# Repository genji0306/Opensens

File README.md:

# Opensens
Opensource Potentiostat
Sau khi chia sẻ điện cực in SPE, Lab em đã nhận được sự nhiều sự quan tâm và liên hệ. Nhóm em nhận thấy là hiện tại việc nghiên cứu về Electrochemistry và Biosensor của các nhóm nghiên cứ ở trong VN còn nhiều khó khăn đặt biệt là về vấn đề thiết bị. Chính vì vậy, lab em quyết định chia sẻ phần nghiên cứu về thiết bị đo điện hoá Potentiostat/Galvanostat cho mọi người, hy vọng có thể giảm bớt khó khăn khi nghiên cứu trong nước Potentiostat/Galvanostat do nhóm DYNLAB- PGS. Thuỷ, thuộc Bộ Môn Điện Hoá, Đại Học Bách Khoa Hà Nội và nhóm PGS. Nguyên, ĐH KHTN HCM - phát triển – tên mã project là OEPS – tên chính thức là Opensens, được phát triển từ cuối năm 2017 với mục tiêu là tạo ra thiết bị đo điện hoá nhỏ gọn tin cậy độ phân giải cao, giá thành hợp lý để triển khai giám sát trên diện rộng. Version đầu tiên dựa trên phiên bản của TS. Dobbelaere và bản sau này của Irving (NCS của Dobbelaere). Phiên bản OEPS V1 dựa trên hardware với một số thay đổi về linh kiện, firmware và phần mềm. Sau 5 năm nghiên cứu, hiện nhóm đã phát triển nhiều Version khác nhau phục vụ cho nghiên cứu về Nguồn điện (Pin), Cảm Biến và giám sát môi trường. 
Trong link chia sẻ là bản OEPS V1/V2, MFO V1 và cả Software gốc/ Software của lab: 
- OEPS V1: Gồm một số tính năng: LSV, CV, CP, CA, Phóng nạp Pin - dải điện áp +-8V 30mA - hiệu chỉnh lỗi và tương thích software bản mới. (DAC 22 bits - độ phân giải 4pA) 
- OEPS V2: Dải điện áp +-12V 250mA - modify chống nhiễu, thay đổi linh kiện giá hợp lý hơn và chỉnh sửa lại Software.
- MFO V1: Phiên bản rút gọn đo 1 phép đo set up sẵn dùng cho y sinh/ môi trường. Có khả năng đo được hầu hết các phép đo LSV,CV,CP,CA, DPV, NPV, EIS(<34khz) (độ phân giải thấp – 12 bits) 
Các phiên bản trên đã được chạy thử nghiệm ít nhất 2 năm và nhiều nhất là từ khi dự án được tiến hành, đã so sánh với thiết bị thương mại như Autolab, Biologic và Palmsens. Các phiên bản khác của lab được tích hơn thêm Pulse technique và EIS sẽ sớm được opensource trong thời gian tiếp theo. Nếu muốn trải nghiệm thiết bị, xin mời mọi người qua DHBK HN ở Hà Nội gặp và Trường DH KHTN HCM ở HCM gặp PGS. Nguyên .

Chi phí linh kiện của thiết bị dao động từ $120-150, tuy nhiên thực tế tuỳ số lượng, đơn vị gia công và thuế nhập khẩu, chi phí sx rơi vào tầm 5-8tr/ thiết bị. Mọi người chỉ cần gửi link và liên hệ bên điện điện tử là được. Cũng chia sẻ luôn, tầm giữa tháng 4 tại bên lab sẽ đặt thêm linh kiện và gia công thiết bị (phiên bản mới) nhưng có chung nhiều linh kiện phiên bản cũ. Vì vậy nếu cần thì bên em có thể đặt giúp mọi người. Chi tiết xin liên hệ sdt: 033. 616.4867 

Ps: do phải tách repo Git để opensource nên dữ liệu sẽ được upload dần từ giờ tới cuối tuần

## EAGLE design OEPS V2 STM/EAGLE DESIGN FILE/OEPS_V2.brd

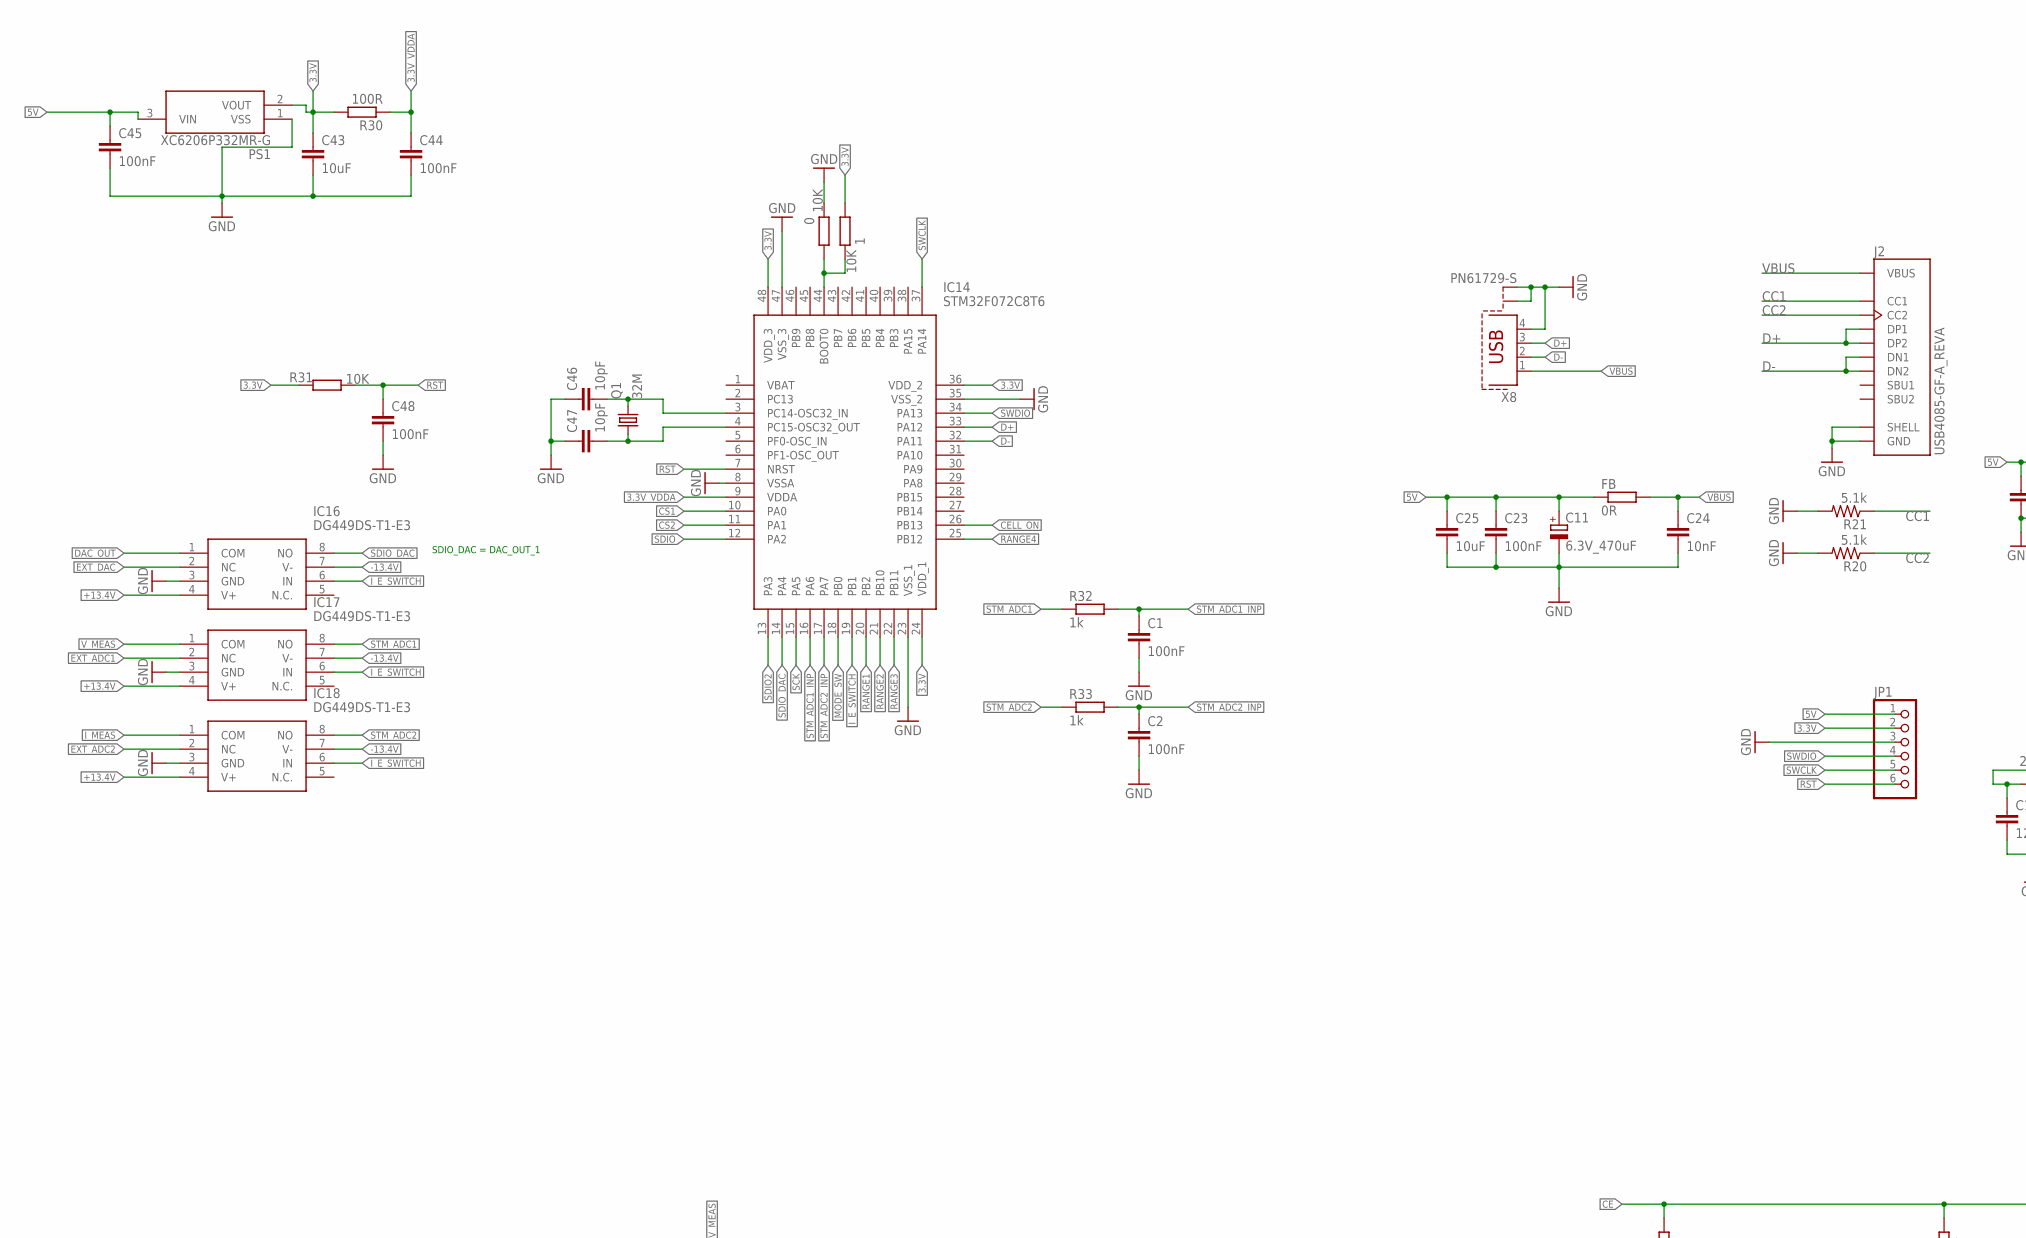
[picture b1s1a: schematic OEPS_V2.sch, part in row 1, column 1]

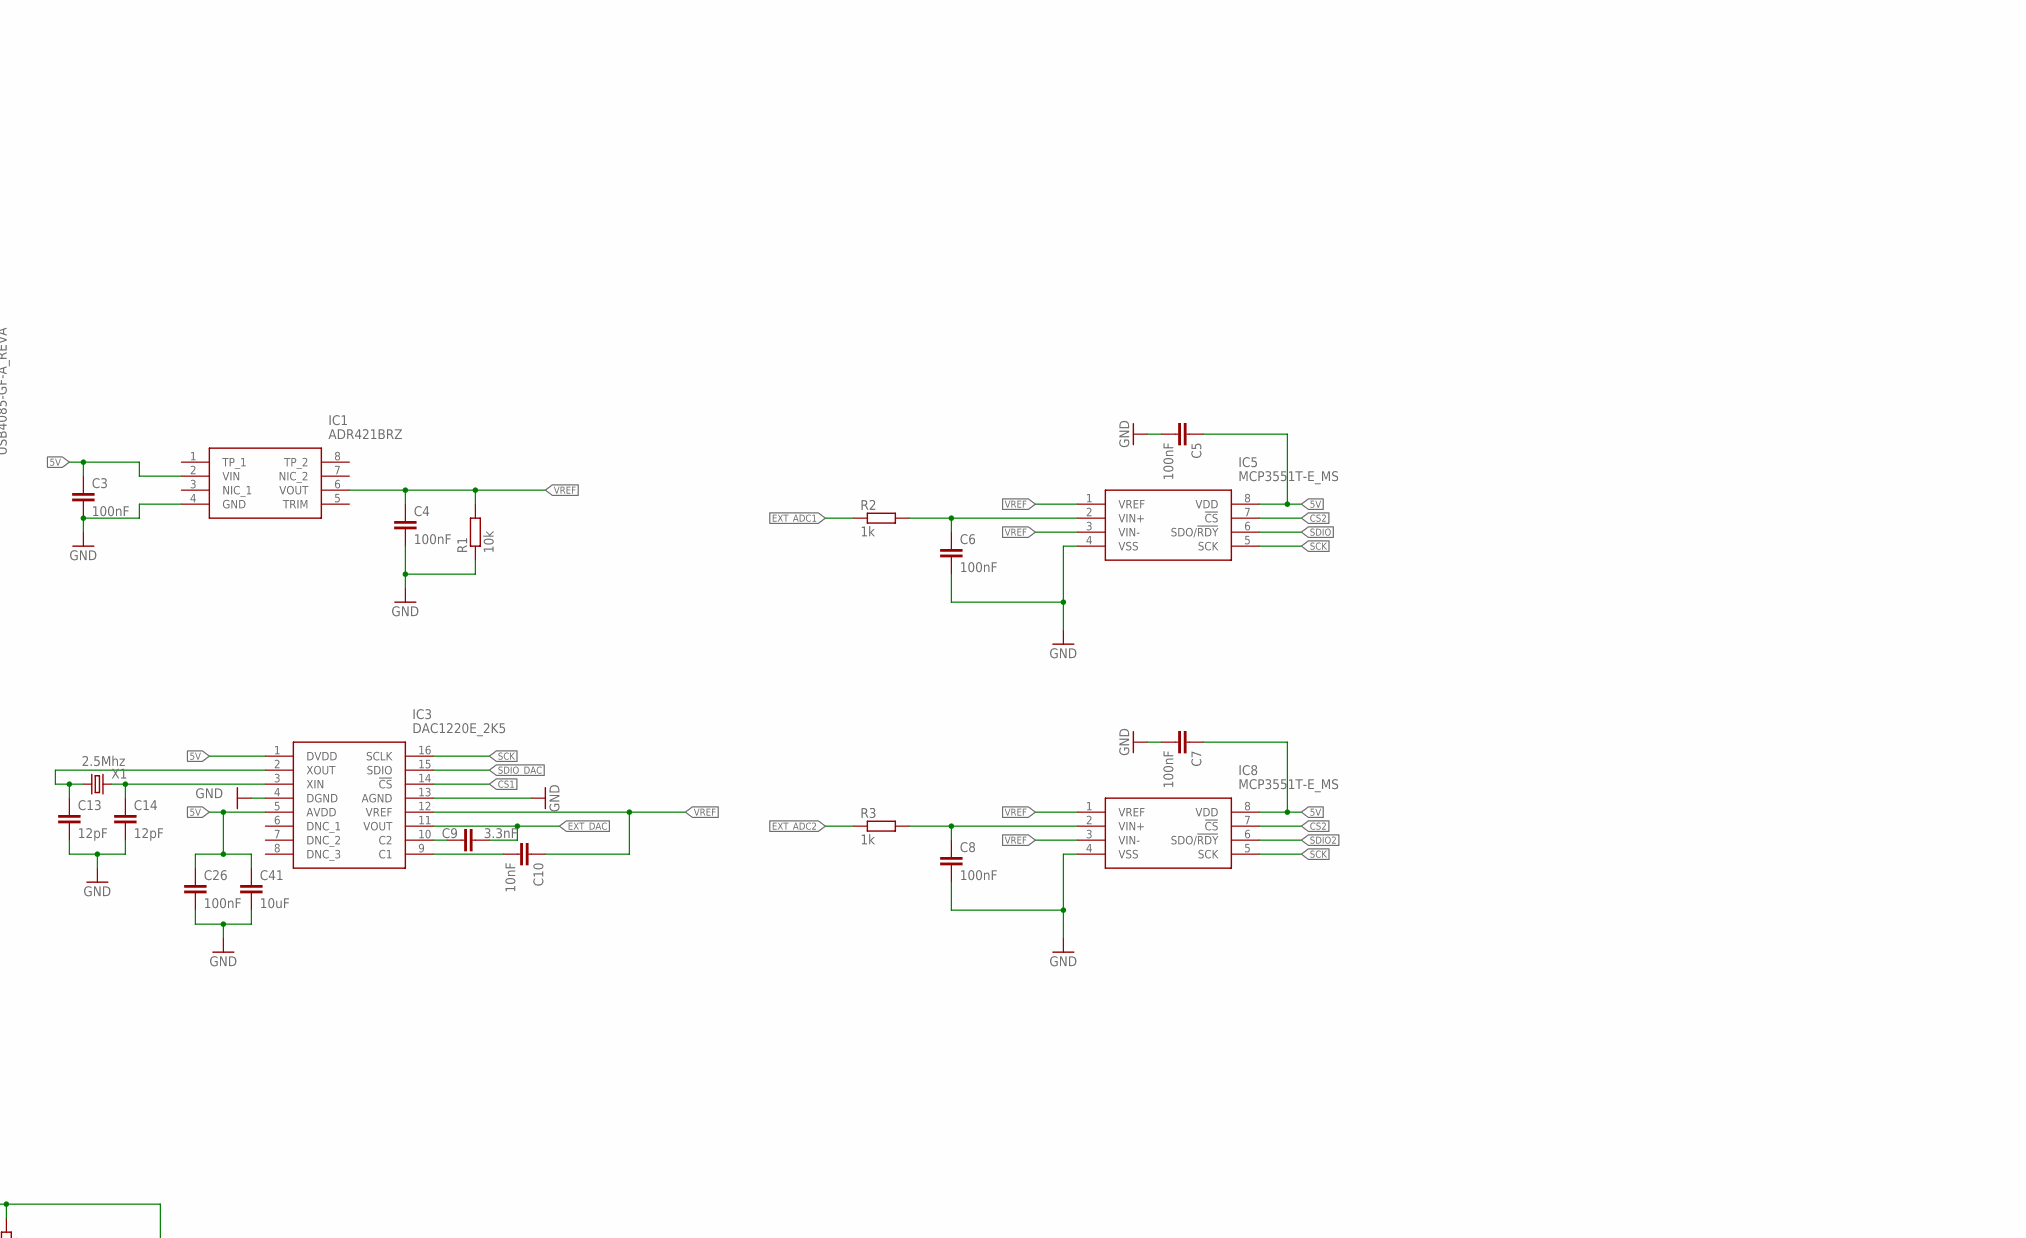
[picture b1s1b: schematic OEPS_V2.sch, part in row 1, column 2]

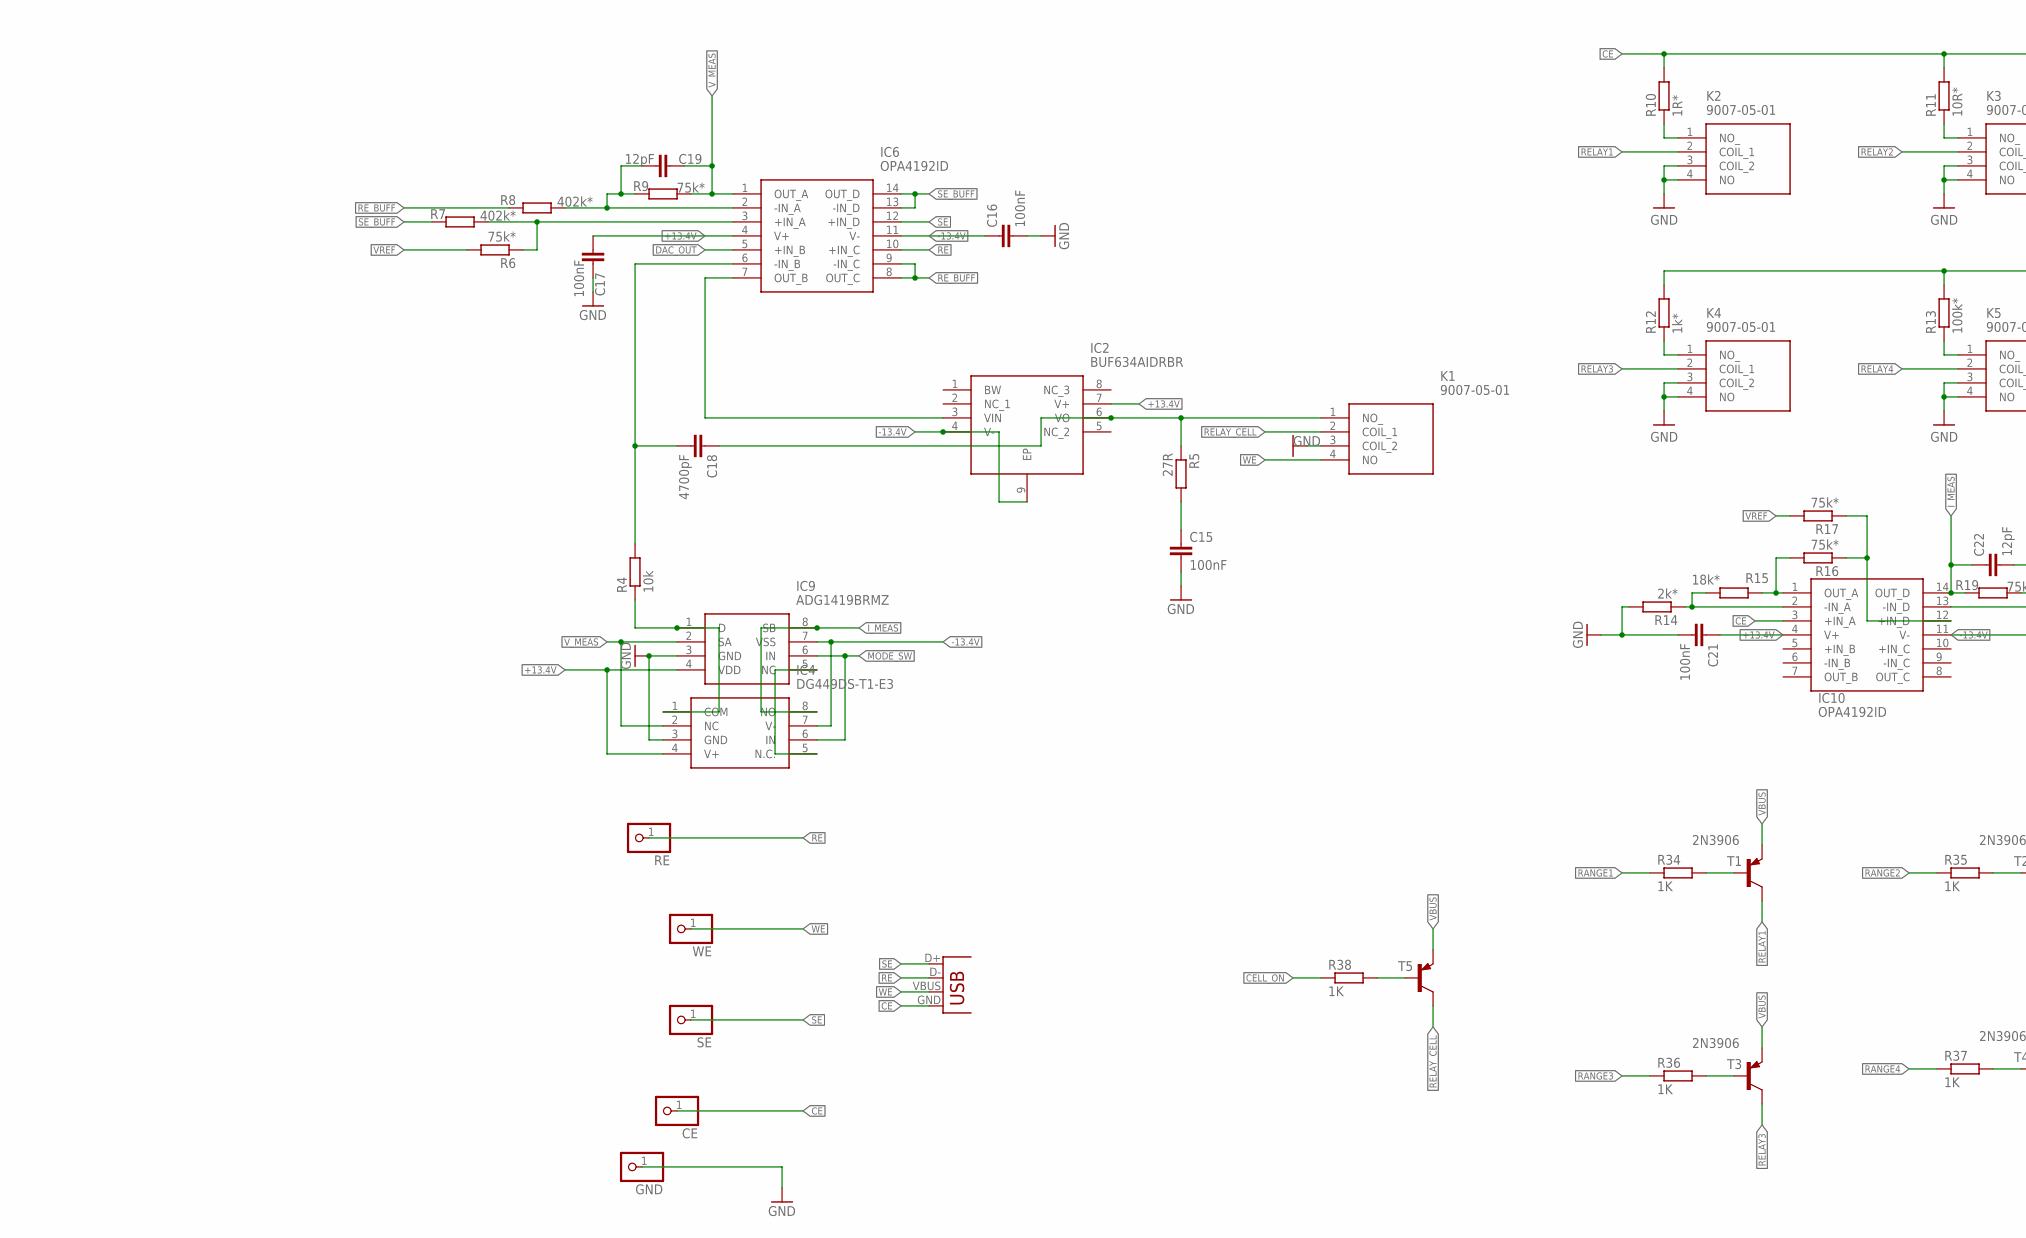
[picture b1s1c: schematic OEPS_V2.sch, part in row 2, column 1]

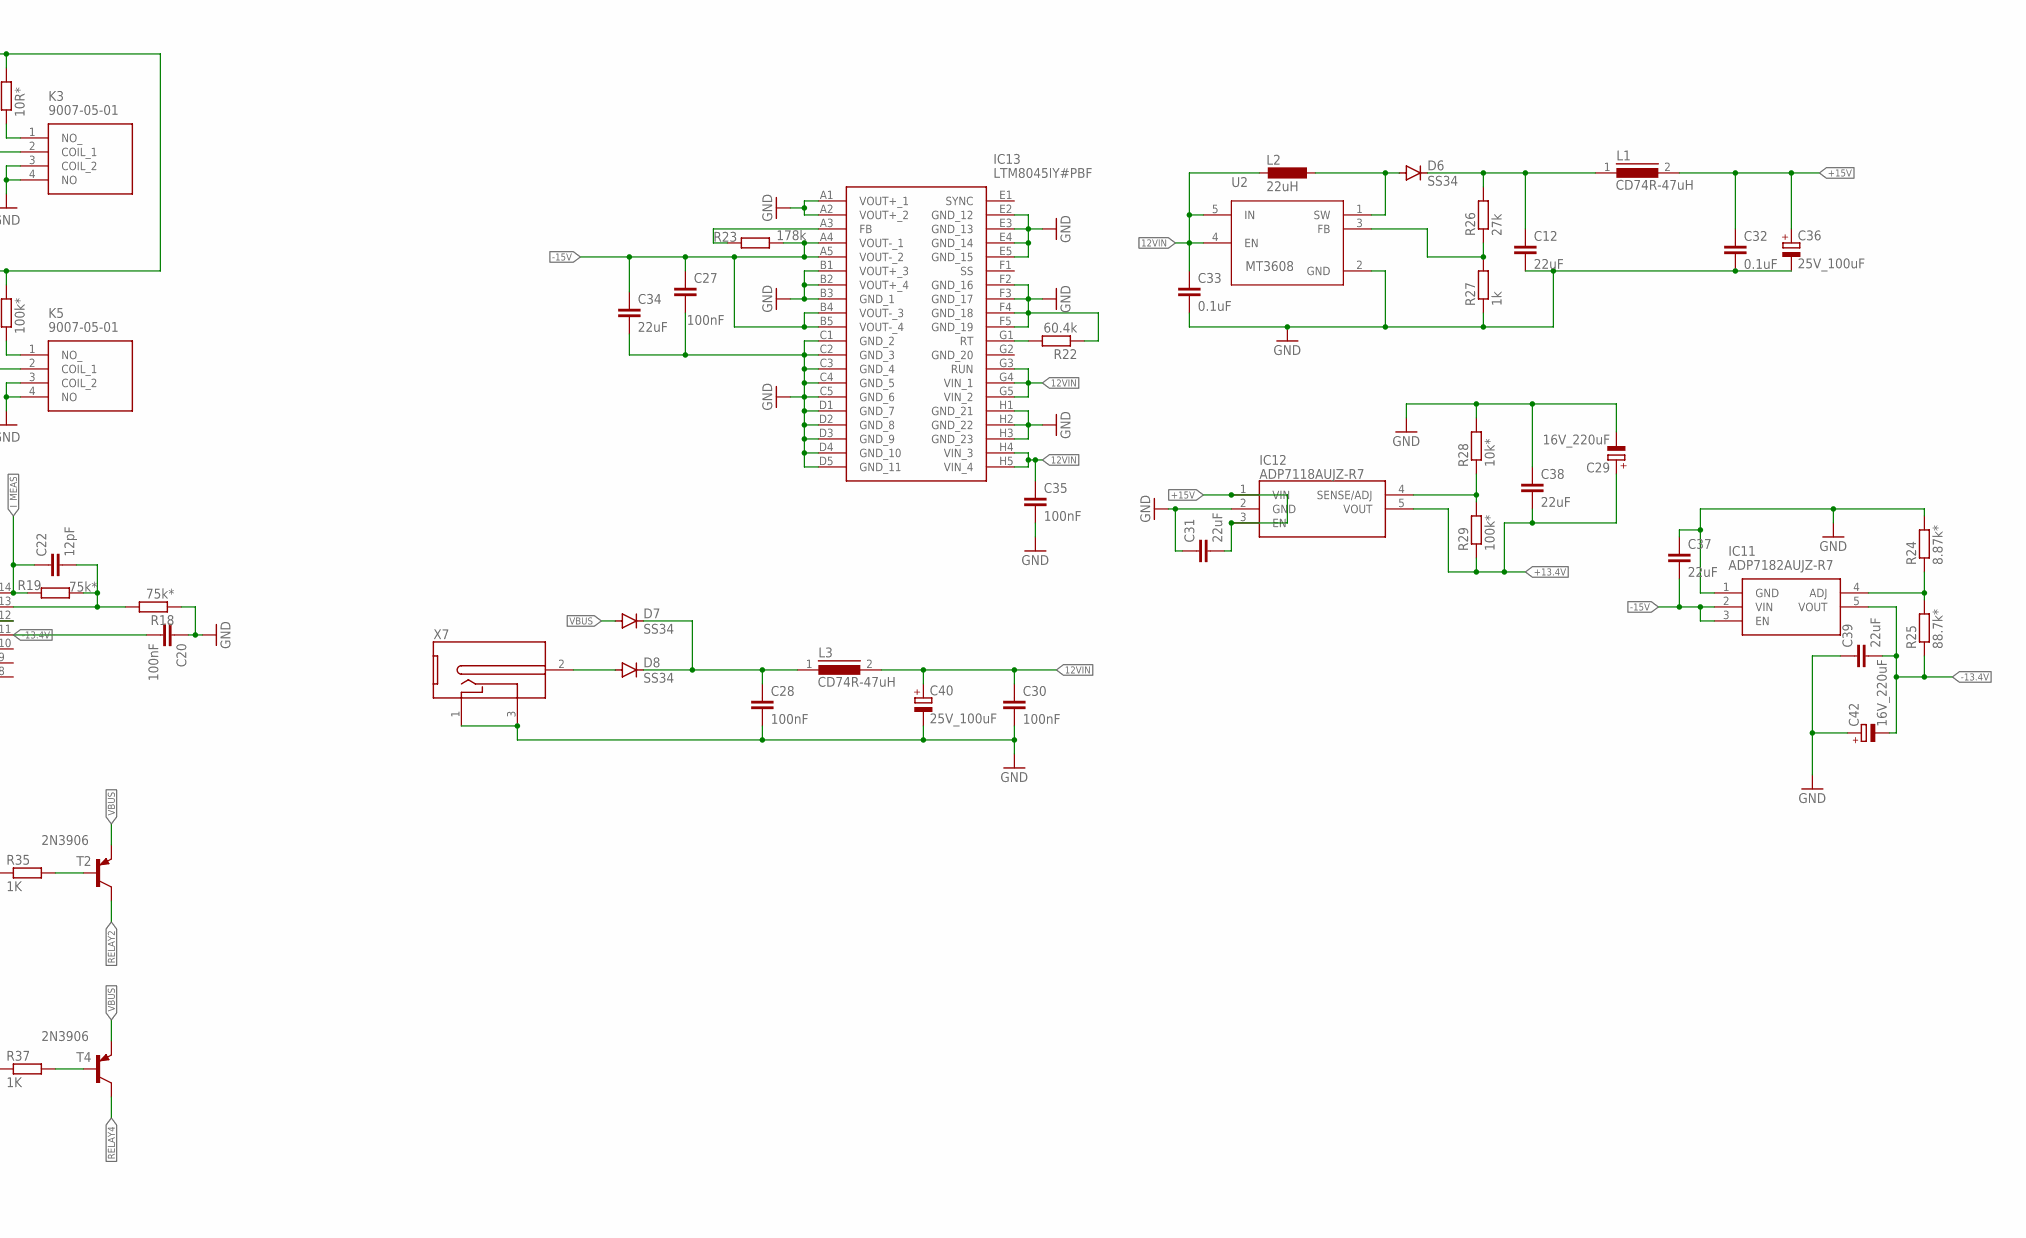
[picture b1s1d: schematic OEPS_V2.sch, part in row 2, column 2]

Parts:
0, 1: 10K; R0603
C1, C2, C3, C4, C5, C6, C7, C8, C15, C16, C17, C20, C21, C23, C26, C44, C45, C48: 100nF; C0603
C9: 3.3nF; C0603
C10, C24: 10nF; C0603
C11: 6.3V_470uF; 153CLV-0605
C12, C31, C34, C37, C38, C39: 22uF; C1206
C13, C14, C19, C22: 12pF; C0603
C18: 4700pF; C0603
C25, C41, C43: 10uF; C0603
C27, C28, C30, C35: 100nF; C0805
C29, C42: 16V_220uF; 153CLV-0605
C32, C33: 0.1uF; C0805
C36, C40: 25V_100uF; 153CLV-0605
C46, C47: 10pF; C0603
CE: PINHD-1X1; 1X01
D6, D7, D8: SS34; DO-214AC
FB: 0R; R0805
GND: PINHD-1X1; 1X01
IC1: ADR421BRZ; SOIC127P600X175-8N
IC2: BUF634AIDRBR; SON65P300X300X100-9N
IC3: DAC1220E_2K5; SOP64P600X175-16N
IC4, IC16, IC17, IC18: DG449DS-T1-E3; SOP65P280X145-8N
IC5, IC8: MCP3551T-E_MS; SOP65P490X110-8N@1
IC6, IC10: OPA4192ID; SOIC127P600X175-14N
IC9: ADG1419BRMZ; SOP65P490X110-8N
IC11: ADP7182AUJZ-R7; SOT95P280X100-5N
IC12: ADP7118AUJZ-R7; SOT95P280X100-5N
IC13: LTM8045IY#PBF; BGA40C127P5X8_625X1125X512
IC14: STM32F072C8T6; QFP50P900X900X160-48N
J2: USB4085-GF-A_REVA; GCT_USB4085-GF-A_REVA
JP1: PINHD-1X6; 1X06
K1, K2, K3, K4, K5: 9007-05-01; 90070501
L1, L3: CD74R-47uH; DR74
L2: 22uH; PIS2816
PS1: XC6206P332MR-G; SOT95P280X130-3N
Q1: 32M; 3.2X2.5_KX-7
R1, R4: 10k; R0603
R2, R3, R27, R32, R33: 1k; R0603
R5: 27R; R0603
R6, R9, R16, R17, R18, R19: 75k*; R0603
R7, R8: 402k*; R0603
R10: 1R*; R0805
R11: 10R*; R0805
R12: 1k*; R0805
R13: 100k*; R0805
R14: 2k*; R0603
R15: 18k*; R0603
R20, R21: 5.1k; R0603
R22: 60.4k; R0603
R23: 178k; R0603
R24: 8.87k*; R0603
R25: 88.7k*; R0603
R26: 27k; R0603
R28: 10k*; R0603
R29: 100k*; R0603
R30: 100R; R0603
R31: 10K; R0603
R34, R35, R36, R37, R38: 1K; R0603
RE: PINHD-1X1; 1X01
SE: PINHD-1X1; 1X01
T1, T2, T3, T4: 2N3906; SOT23-BEC
T5: MMBT3906LT1-PNP-SOT23-BEC; SOT23-BEC
U2: MT3608; SOT95P280X145-6N
WE: PINHD-1X1; 1X01
X1: 2.5Mhz; HC49
X6: USB-A-H
X7: DC-2.1MM-5MM; DC-21MM
X8: PN61729-S

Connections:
3.3V: 1.2, C43.1, IC14.24 (VDD_1), IC14.36 (VDD_2), IC14.48 (VDD_3), JP1.2, PS1.2 (VOUT), R30.2, R31.2
3.3V_VDDA: C44.1, IC14.9 (VDDA), R30.1
5V: C3.1, C5.1, C7.1, C11.+, C23.1, C25.1, C26.1, C41.1, C45.1, FB.1, IC1.2 (VIN), IC3.1 (DVDD), IC3.5 (AVDD), IC5.8 (VDD), IC8.8 (VDD), JP1.1, PS1.3 (VIN)
12VIN: C30.1, C33.1, C35.1, C40.+, IC13.G3 (RUN), IC13.G4 (VIN_1), IC13.G5 (VIN_2), IC13.H4 (VIN_3), IC13.H5 (VIN_4), L2.2, L3.2, U2.4 (EN), U2.5 (IN)
+13.4V: C17.2, C21.1, C29.+, C38.2, IC2.7 (V+), IC4.4 (V+), IC6.4 (V+), IC9.4 (VDD), IC10.4 (V+), IC12.5 (VOUT), IC16.4 (V+), IC17.4 (V+), IC18.4 (V+), R29.1
+15V: C31.2, C32.1, C36.+, IC12.1 (VIN), IC12.3 (EN), L1.2
-13.4V: C16.1, C20.1, C39.2, C42.-, IC2.4 (V-), IC2.9 (EP), IC4.7 (V-), IC6.11 (V-), IC9.7 (VSS), IC10.11 (V-), IC11.5 (VOUT), IC16.7 (V-), IC17.7 (V-), IC18.7 (V-), R25.1
-15V: C27.1, C34.1, C37.2, IC11.2 (VIN), IC11.3 (EN), IC13.A4 (VOUT-_1), IC13.A5 (VOUT-_2), IC13.B4 (VOUT-_3), IC13.B5 (VOUT-_4), R23.2
CC1: J2.A5 (CC1), R21.1
CC2: J2.B5 (CC2), R20.1
CE: CE.1, IC10.3 (+IN_A), R10.2, R11.2, R12.2, R13.2, X6.GND
CELL_ON: IC14.26 (PB13), R38.1
CS1: IC3.14 (!CS), IC14.10 (PA0)
CS2: IC5.7 (!CS), IC8.7 (!CS), IC14.11 (PA1)
D+: IC14.33 (PA12), J2.A6 (DP1), J2.B6 (DP2), X8.3
D-: IC14.32 (PA11), J2.A7 (DN1), J2.B7 (DN2), X8.2
DAC_OUT: IC6.5 (+IN_B), IC16.1 (COM)
EXT_ADC1: IC17.2 (NC), R2.1
EXT_ADC2: IC18.2 (NC), R3.1
EXT_DAC: C9.1, IC3.11 (VOUT), IC16.2 (NC)
GND: 0.1, C1.2, C2.2, C3.2, C4.2, C5.2, C6.2, C7.2, C8.2, C11.-, C12.2, C13.2, C14.2, C15.2, C16.2, C17.1, C20.2, C21.2, C23.2, C24.2, C25.2, C26.2, C27.2, C28.2, C29.-, C30.2, C31.1, C32.2, C33.2, C34.2, C35.2, C36.-, C37.1, C38.1, C39.1, C40.-, C41.2, C42.+, C43.2, C44.2, C45.2, C46.1, C47.1, C48.2, GND.1, IC1.4 (GND), IC3.4 (DGND), IC3.13 (AGND), IC4.3 (GND), IC5.4 (VSS), IC8.4 (VSS), IC9.3 (GND), IC11.1 (GND), IC12.2 (GND), IC13.A1 (VOUT+_1), IC13.A2 (VOUT+_2), IC13.B1 (VOUT+_3), IC13.B2 (VOUT+_4), IC13.B3 (GND_1), IC13.C1 (GND_2), IC13.C2 (GND_3), IC13.C3 (GND_4), IC13.C4 (GND_5), IC13.C5 (GND_6), IC13.D1 (GND_7), IC13.D2 (GND_8), IC13.D3 (GND_9), IC13.D4 (GND_10), IC13.D5 (GND_11), IC13.E2 (GND_12), IC13.E3 (GND_13), IC13.E4 (GND_14), IC13.E5 (GND_15), IC13.F2 (GND_16), IC13.F3 (GND_17), IC13.F4 (GND_18), IC13.F5 (GND_19), IC13.H1 (GND_21), IC13.H2 (GND_22), IC13.H3 (GND_23), IC14.8 (VSSA), IC14.23 (VSS_1), IC14.35 (VSS_2), IC14.47 (VSS_3), IC16.3 (GND), IC17.3 (GND), IC18.3 (GND), J2.A1 (GND), J2.A12 (GND), J2.B1 (GND), J2.B12 (GND), J2.P1 (SHELL), J2.P2 (SHELL), J2.P3 (SHELL), J2.P4 (SHELL), JP1.3, K1.3 (COIL_2), K2.3 (COIL_2), K2.4 (NO), K3.3 (COIL_2), K3.4 (NO), K4.3 (COIL_2), K4.4 (NO), K5.3 (COIL_2), K5.4 (NO), PS1.1 (VSS), R1.1, R14.2, R18.1, R20.2, R21.2, R22.1, R24.2, R27.1, R28.2, U2.2 (GND), X7.1, X7.3 (2), X8.4, X8.S1, X8.S2
I_E_SWITCH: IC14.19 (PB1), IC16.6 (IN), IC17.6 (IN), IC18.6 (IN)
I_MEAS: C22.1, IC4.8 (NO), IC9.8 (SB), IC10.14 (OUT_D), IC18.1 (COM), R19.2
MODE_SW: IC4.6 (IN), IC9.6 (IN), IC14.18 (PB0)
unnamed: C6.1, IC5.2 (VIN+), R2.2
unnamed: C8.1, IC8.2 (VIN+), R3.2
unnamed: R34.2, T1.B
unnamed: C46.2, IC14.3 (PC14-OSC32_IN), Q1.3 (2)
unnamed: C14.1, IC3.3 (XIN), X1.2
unnamed: C13.1, IC3.2 (XOUT), X1.1
unnamed: C9.2, IC3.10 (C2)
unnamed: C10.2, IC3.9 (C1)
unnamed: IC4.1 (COM), IC9.1 (D), R4.1
unnamed: C18.2, IC6.6 (-IN_B), R4.2
unnamed: IC2.3 (VIN), IC6.7 (OUT_B)
unnamed: C18.1, IC2.6 (VO), K1.1 (NO_), R5.1
unnamed: C15.1, R5.2
unnamed: IC4.5 (N.C.), IC9.5 (NC)
unnamed: IC6.3 (+IN_A), R6.1, R7.1
unnamed: C19.2, IC6.2 (-IN_A), R8.1, R9.2
unnamed: K2.1 (NO_), R10.1
unnamed: IC10.1 (OUT_A), R15.1, R16.2
unnamed: K3.1 (NO_), R11.1
unnamed: IC10.2 (-IN_A), R14.1, R15.2
unnamed: K4.1 (NO_), R12.1
unnamed: C12.1, D6.C, L1.1, R26.2
unnamed: K5.1 (NO_), R13.1
unnamed: IC10.12 (+IN_D), R16.1, R17.1
unnamed: C28.1, D7.C, D8.C, L3.1
unnamed: C22.2, IC10.13 (-IN_D), R18.2, R19.1
unnamed: IC11.4 (ADJ), R24.1, R25.2
unnamed: D8.A, X7.2 (3)
unnamed: IC12.4 (SENSE/ADJ), R28.1, R29.2
unnamed: C47.2, IC14.4 (PC15-OSC32_OUT), Q1.1
unnamed: 0.2, 1.1, IC14.44 (BOOT0)
unnamed: R35.2, T2.B
unnamed: IC13.G1 (RT), R22.2
unnamed: IC13.A3 (FB), R23.1
unnamed: R36.2, T3.B
unnamed: R37.2, T4.B
unnamed: R38.2, T5.B
unnamed: D6.A, L2.1, U2.1 (SW)
unnamed: R26.1, R27.2, U2.3 (FB)
RANGE1: IC14.20 (PB2), R34.1
RANGE2: IC14.21 (PB10), R35.1
RANGE3: IC14.22 (PB11), R36.1
RANGE4: IC14.25 (PB12), R37.1
RE: IC6.10 (+IN_C), RE.1, X6.D-
RELAY1: K2.2 (COIL_1), T1.C
RELAY2: K3.2 (COIL_1), T2.C
RELAY3: K4.2 (COIL_1), T3.C
RELAY4: K5.2 (COIL_1), T4.C
RELAY_CELL: K1.2 (COIL_1), T5.C
RE_BUFF: IC6.8 (OUT_C), IC6.9 (-IN_C), R8.2
RST: C48.1, IC14.7 (NRST), JP1.6, R31.1
SCK: IC3.16 (SCLK), IC5.5 (SCK), IC8.5 (SCK), IC14.15 (PA5)
SDIO: IC5.6 (SDO/!RDY), IC14.12 (PA2)
SDIO2: IC8.6 (SDO/!RDY), IC14.13 (PA3)
SDIO_DAC: IC3.15 (SDIO), IC14.14 (PA4), IC16.8 (NO)
SE: IC6.12 (+IN_D), SE.1, X6.D+
SE_BUFF: IC6.13 (-IN_D), IC6.14 (OUT_D), R7.2
STM_ADC1: IC17.8 (NO), R32.1
STM_ADC1_INP: C1.1, IC14.16 (PA6), R32.2
STM_ADC2: IC18.8 (NO), R33.1
STM_ADC2_INP: C2.1, IC14.17 (PA7), R33.2
SWCLK: IC14.37 (PA14), JP1.5
SWDIO: IC14.34 (PA13), JP1.4
VBAT: IC14.1 (VBAT)
VBUS: C24.1, D7.A, FB.2, J2.A4 (VBUS), J2.A9 (VBUS), J2.B4 (VBUS), J2.B9 (VBUS), T1.E, T2.E, T3.E, T4.E, T5.E, X8.1
VREF: C4.1, C10.1, IC1.6 (VOUT), IC3.12 (VREF), IC5.1 (VREF), IC5.3 (VIN-), IC8.1 (VREF), IC8.3 (VIN-), R1.2, R6.2, R17.2
V_MEAS: C19.1, IC4.2 (NC), IC6.1 (OUT_A), IC9.2 (SA), IC17.1 (COM), R9.1
WE: K1.4 (NO), WE.1, X6.VBUS

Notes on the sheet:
SDIO_DAC = DAC_OUT_1

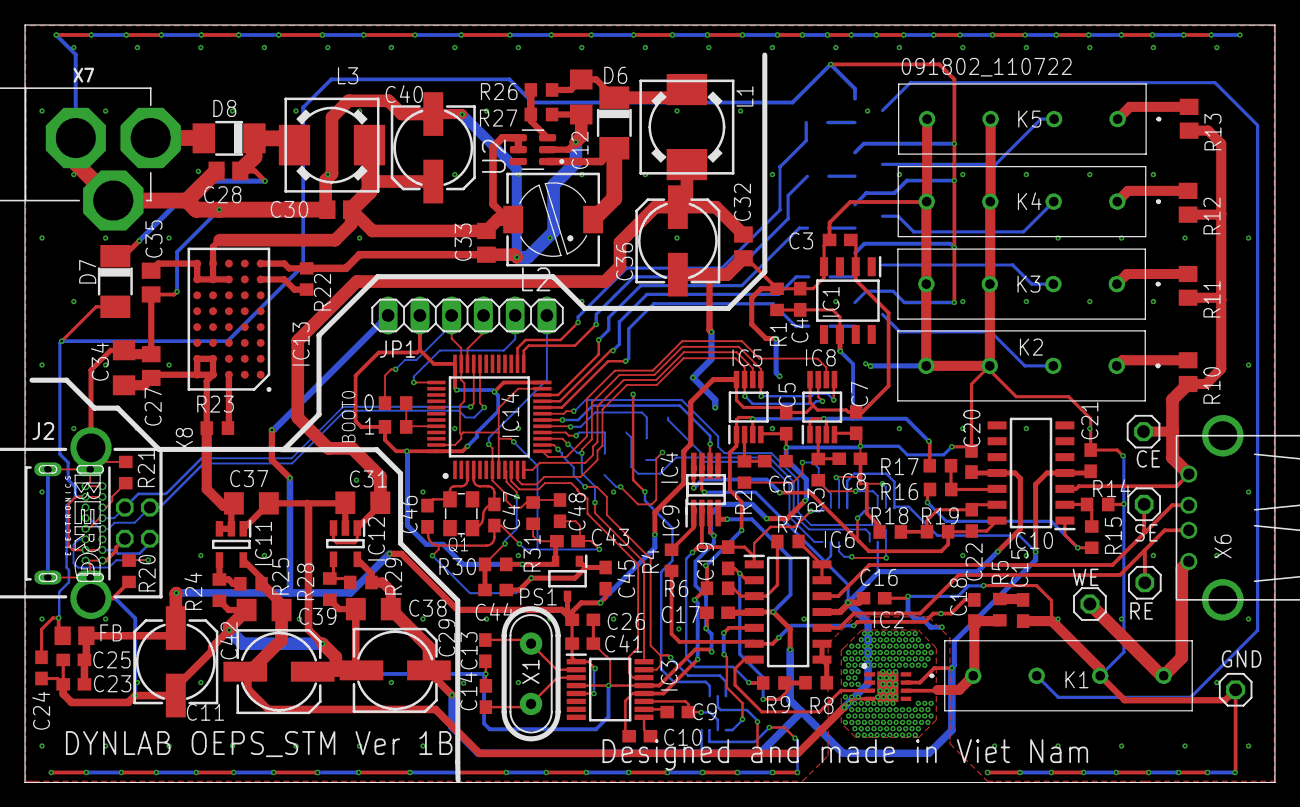
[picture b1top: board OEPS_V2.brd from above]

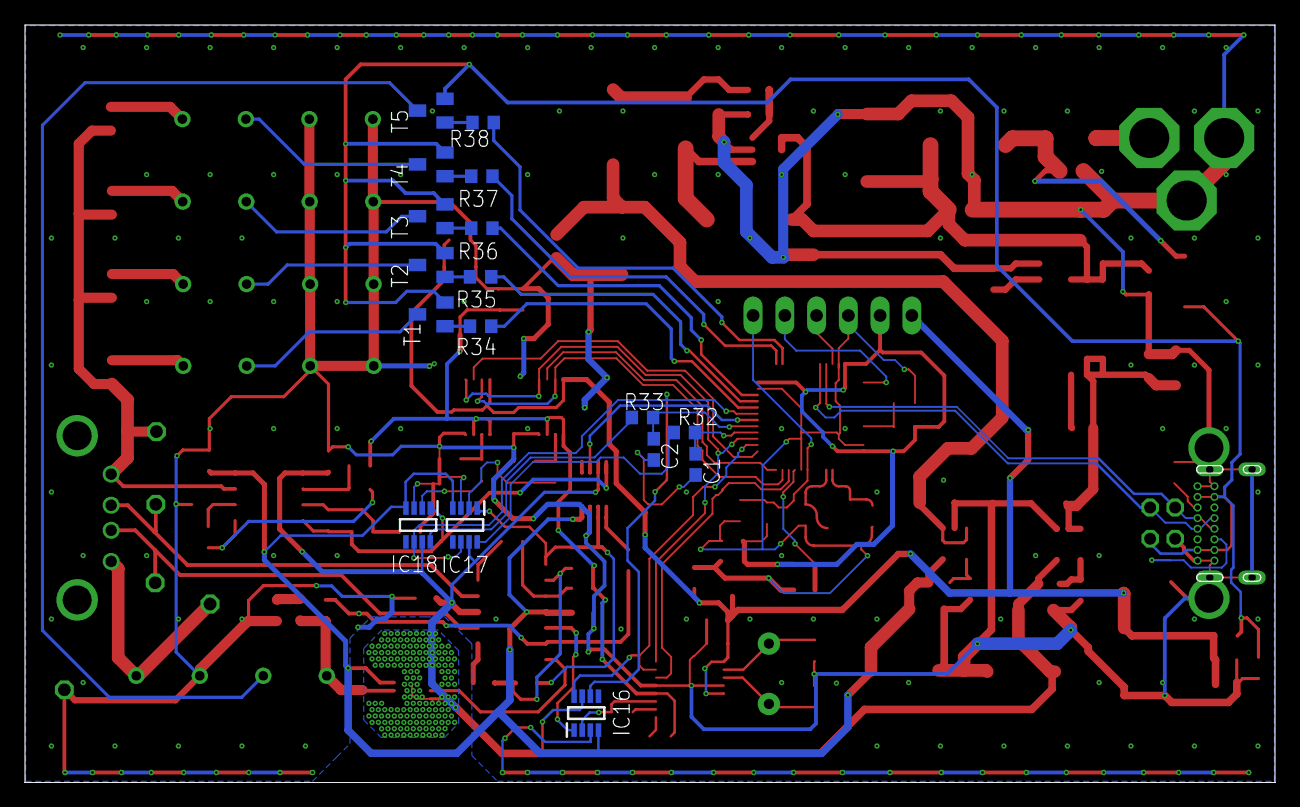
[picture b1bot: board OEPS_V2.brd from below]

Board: 2 copper layers, 100.0 x 60.6 mm, 135 parts (17 on the bottom side), 91 nets.

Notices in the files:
parts and their libraries:
crystal-geyer_V1_0: Copyright: Geyer-Electronic
